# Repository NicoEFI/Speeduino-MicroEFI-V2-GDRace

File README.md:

# Speeduino-MicroEFI-V2-GDRace

Use Speeduino Firmware

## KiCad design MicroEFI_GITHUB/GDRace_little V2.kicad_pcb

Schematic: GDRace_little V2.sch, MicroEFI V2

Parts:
180k1, 180k2, 330k1, 330k2: R_Pack04; R_Array_Convex_4x0603
C1, C3: 1u; C_1206_HandSoldering
C2, C5: 22u; C_1206_HandSoldering
C4, C15, C18, C19, C20, C21, C22, C23, C30, C36: 0.1u; condo_C_1206_3216Metric_Pad1.42x1.75mm_HandSolder
C6: 100n; condo_C_1206_3216Metric_Pad1.42x1.75mm_HandSolder
C7: 100u; TantalC_SizeC_EIA-6032_HandSoldering
C11: 0.1uF; condo_C_1206_3216Metric_Pad1.42x1.75mm_HandSolder
C12: 4.7nF; condo_C_1206_3216Metric_Pad1.42x1.75mm_HandSolder
C13: 470p; condo_C_1206_3216Metric_Pad1.42x1.75mm_HandSolder
C14: 1u; condo_C_1206_3216Metric_Pad1.42x1.75mm_HandSolder
C16: 1n; condo_C_1206_3216Metric_Pad1.42x1.75mm_HandSolder
C17: 10n; condo_C_1206_3216Metric_Pad1.42x1.75mm_HandSolder
C24, C25, C26, C27, C28, C29, C31, C37: 0.22u; condo_C_1206_3216Metric_Pad1.42x1.75mm_HandSolder
D1: V68MLA1206H; Fuse_SMD1206_Reflow
D2, D7: Schottly-SS12; D_SMA_Handsoldering
D3: 3SMAJ5931B; do214ac
D4, D5, D6, D8, D11, D12, D13: 1N4001; D_MELF
D9: ZENER; do214ac
D10: 1N5819; SOD-123
D14: LED; LED_1206_3216Metric
F1: Polyfuse; Fuse_Bourns_MF-SM_9.5x6.71mm
GNDREF1, GNDREF2: CONN_01X01; MountingHole_3.2mm_M3_Pad_Via
J2: USB; JST_PH_B4B-PH-K_1x04_P2.00mm_Vertical
JP1, JP2: JUMPER; SolderJumper-2_P1.3mm_Open_RoundedPad1.0x1.5mm
JP3, JP4, JP5, JP7, JP8: JUMPER3; SolderJumper-3_P1.3mm_Open_RoundedPad1.0x1.5mm_NumberLabels
L1, L2, L3: 10uH; L_1206_3216Metric_Pad1.42x1.75mm_HandSolder
Q1, Q2, Q3: VND5N07
Q6, Q7: ISL9V5036S3S; TO-263-ingnition
R1: 470; resistance_R_1206_3216Metric_Pad1.42x1.75mm_HandSolder
R2, R4, R5, R9, R20, R41, R42: 200; resistance_R_1206_3216Metric_Pad1.42x1.75mm_HandSolder
R3, R11, R47: 2.2k; resistance_R_1206_3216Metric_Pad1.42x1.75mm_HandSolder
R6, R22: 10k; resistance_R_1206_3216Metric_Pad1.42x1.75mm_HandSolder
R10: 120; resistance_R_1206_3216Metric_Pad1.42x1.75mm_HandSolder
R13, R15, R23, R24, R32: 1k; resistance_R_1206_3216Metric_Pad1.42x1.75mm_HandSolder
R16, R17, R21, R43: 47k; resistance_R_1206_3216Metric_Pad1.42x1.75mm_HandSolder
R18, R19: 10k; R_2010_5025Metric
R25, R26: 100k; resistance_R_1206_3216Metric_Pad1.42x1.75mm_HandSolder
R27, R28, R45: 68k; resistance_R_1206_3216Metric_Pad1.42x1.75mm_HandSolder
R29, R30: 15R; resistance_R_1206_3216Metric_Pad1.42x1.75mm_HandSolder
R31: 3.9k; resistance_R_1206_3216Metric_Pad1.42x1.75mm_HandSolder
R33, R34: 2.49k; resistance_R_1206_3216Metric_Pad1.42x1.75mm_HandSolder
R35, R36, R37, R38, R39, R40, R44, R46: 470R; resistance_R_1206_3216Metric_Pad1.42x1.75mm_HandSolder
U1: LM2940T-5.0; sot223
U2: SN65HVD230; SOIC-8_3.9x4.9mm_P1.27mm
U3: MPX4250; MPXH6250A6U
U4: Molex48; connecteurMolex48
U5: Teensy3.5; Teensy35_36_sansSMD
U6, U7, U9, U13: IRLML0030TRPbF; IRLML0030_sot23
U8: MAX9926; QSOP-16_3.9x4.9mm_P0.635mm
U10: TC4424; SOIC-8_3.9x4.9mm_P1.27mm
U11, U12: LMV324; TSSOP-14_4.4x5mm_P0.65mm

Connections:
/3.3V: D10.1, R3.1, R11.1, R13.1, R15.1, R47.1, U5.15, U5.26, U11.4, U12.4
/5V: C7.1, C14.1, C15.1, C17.1, D9.1, F1.1, JP3.3, L2.1, R1.1, U5.53, U8.14 (vcc), U10.6 (VDD)
/5VSENSOR: C11.1, L2.2, R33.1, R34.1, U3.2, U4.2A1, U4.2A2, U4.2A3, U4.2A4
/12VPUISSANCE: C2.1, D2.1, D3.1, D7.1, JP3.1, U1.1
/12V_BATT_APRES_RELAIS: C1.1, D11.1 (K), L1.1, R31.1, U4.2L3, U4.2L4
/BARO: C19.1, JP2.2, R36.2
/BARO_3.3V: U5.42, U11.1, U11.2
/BARO_5V: 180k1.4, C25.1, R36.1
/BATTERY_REF_3.3V: U5.43, U11.8, U11.9
/BATTERY_REF_5V: 180k1.1, C26.1, R37.1
/BOOST: D11.2 (A), Q1.2 (D), U4.2C3
/BOOST_CPU: R5.1, R45.1, U5.48
/Btn_carto: D6.1 (K), U4.2K1
/Btn_carto_CPU: D6.2 (A), D8.1 (K), R11.2, U5.14
/Btn_depart: D4.1 (K), U4.2K2
/Btn_depart_CPU: D4.2 (A), D5.1 (K), R3.2, U5.16
/CAN_H: JP1.1, JP7.1, U2.7
/CAN_L: JP8.1, R10.2, U2.6
/CAN_RX_CPU: U2.4, U5.6
/CAN_TX_CPU: U2.1, U5.5
/CLT_3.3V: U5.47, U12.8, U12.9
/CLT_5V: 180k2.1, C28.1, R39.1
/CMD_RELAY_FUEL: U4.2G3, U6.3
/CMD_RELAY_FUEL_CPU: R41.1, U5.35
/D+: J2.3, U5.87
/D-: J2.2, U5.88
/DASH_CANH_TX_CPU: JP7.2, U4.2C1
/DASH_CANL_RX_CPU: JP8.2, U4.2C2
/FAN1: U4.2G1, U7.3
/FAN1_CPU: R9.1, U5.19
/FAN2: U4.2H1, U13.3
/FAN2_CPU: R42.1, U5.18
/GNDSENSOR: C11.2, C13.2, C18.2, C19.2, C20.2, C21.2, C22.2, C23.2, C24.2, C25.2, C26.2, C27.2, C28.2, C29.2, C30.2, C31.2, C36.2, C37.2, L3.2, R32.2, U3.3, U4.2B1, U4.2B2, U4.2B3, U4.2B4
/IAT_3.3V: U5.45, U12.13, U12.14
/IAT_5V: 180k2.2, C29.1, R40.1
/IGN_A_CPU: R23.1, U5.21
/IGN_B_CPU: R24.1, U5.20
/IGN_cyl_1_4: Q6.2, U4.2M4
/IGN_cyl_2_3: Q7.2, U4.2M3
/INJ_A_CPU: R2.1, R27.1, U5.22
/INJ_B_CPU: R4.1, R28.1, U5.30
/INJ_cyl_1_4: Q2.2 (D), U4.2M2
/INJ_cyl_2_3: Q3.2 (D), U4.2M1
/MAP: C30.1, R44.2, U4.2F3
/MAP_3.3V: U5.46, U12.6, U12.7
/MAP_5V: 180k2.3, C31.1, R44.1
/P_Oil_sw: D12.1 (K), U4.2K3
/P_Oil_sw_CPU: D12.2 (A), D13.1 (K), R47.2, U5.17
/RESET: C12.1, D10.2, R13.2, U5.29
/RX2_CPU: JP8.3, U5.12
/SMOT++: R18.1, U4.2D2
/SMOT--: R19.1, U4.2D1
/SMOT_CPU: R15.2, U5.8, U8.4 (out1)
/TACHO: R22.2, U4.2G2, U9.3
/TACHO_CPU: R20.1, U5.13
/TAIR: C23.1, R34.2, R40.2, U4.2E2
/TEAU: C22.1, R33.2, R39.2, U4.2E1
/TPS1: C21.1, R38.2, U4.2F1
/TPS1_3.3V: U5.41, U11.13, U11.14
/TPS1_5V: 180k1.2, C27.1, R38.1
/TX2_CPU: JP7.3, U5.11
/VARlaunch: C18.1, R35.2, U4.2F2
/VARlaunch_3.3V: U5.44, U11.6, U11.7
/VARlaunch_5V: 180k1.3, C24.1, R35.1
/VUSB: J2.1, U5.54
/WBO2: C36.1, R46.2, U4.2E3
/WBO2_3.3V: U5.49, U12.1, U12.2
/WBO2_5V: 180k2.4, C37.1, R46.1
GNDREF: 330k1.5, 330k1.6, 330k1.7, 330k1.8, 330k2.5, 330k2.6, 330k2.7, 330k2.8, C1.2, C2.2, C3.2, C4.2, C5.2, C6.2, C7.2, C12.2, C14.2, C15.2, C17.2, D1.2, D3.2, D5.2 (A), D8.2 (A), D9.2, D13.2 (A), D14.1, GNDREF1.1, GNDREF2.1, J2.4, L3.1, Q1.3 (S), Q2.3 (S), Q3.3 (S), Q6.3, Q7.3, R6.2, R16.2, R17.2, R21.2, R25.1, R26.2, R27.2, R28.2, R43.2, R45.2, U1.2, U1.4, U2.2, U4.2L1, U4.2L2, U5.1, U5.27, U5.39, U6.2, U7.2, U8.1 (int_thrs1), U8.3 (bias1), U8.6 (bias2), U8.8 (int_thrs2), U8.11 (gnd), U8.13 (zero_en), U9.2, U10.3 (GND), U11.11, U12.11, U13.2
unnamed: 180k1.5, 330k1.4, U11.3
unnamed: 180k1.6, 330k1.3, U11.5
unnamed: 180k1.7, 330k1.2, U11.12
unnamed: 180k1.8, 330k1.1, U11.10
unnamed: 180k2.5, 330k2.4, U12.3
unnamed: 180k2.6, 330k2.3, U12.5
unnamed: 180k2.7, 330k2.2, U12.12
unnamed: 180k2.8, 330k2.1, U12.10
unnamed: C3.1, C4.1, D1.1, D2.2, L1.2
unnamed: C5.1, C6.1, D7.2, F1.2, U1.3
unnamed: C13.1, JP2.1, U3.4
unnamed: C16.1, R19.2, U8.15 (in1-)
unnamed: C16.2, R18.2, U8.16 (in1+)
unnamed: C20.1, R31.2, R32.1, R37.2
unnamed: D14.2, R1.2
unnamed: JP1.2, R10.1
unnamed: JP3.2, R22.1
unnamed: JP4.1, U10.7 (OUTA)
unnamed: JP4.2, R29.1
unnamed: JP4.3, R23.2, R25.2, U10.2 (INA)
unnamed: JP5.1, U10.5 (OUTB)
unnamed: JP5.2, R30.1
unnamed: JP5.3, R24.2, R26.1, U10.4 (INB)
unnamed: Q1.1 (G), R5.2
unnamed: Q2.1 (G), R2.2
unnamed: Q3.1 (G), R4.2
unnamed: Q6.1, R29.2
unnamed: Q7.1, R30.2
unnamed: R6.1, U2.8
unnamed: R16.1, R41.2, U6.1
unnamed: R9.2, R17.1, U7.1
unnamed: R20.2, R21.1, U9.1
unnamed: R42.2, R43.1, U13.1

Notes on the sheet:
Bouton switch
Capteur pression
Capteur régime et cam
Alimentation
VND14NV04
12V_BATT_APRES_RELAIS_CONTACT
BATT
Fusible
Ventilo
ex : Pilotage ventilo 1
Interrupteur alim calculateur
FGP3440G2_F085 ISL9V5036S3S TO-263-2
1N5819HW-7-F
connecteur USB MUSB-D111-30 mouser + Connecteur micro-USB B mâle à souder (gotronic)
jack 3.5 LUMBERG = 1502 02 CUI Devices = SJ5-43502PM cable DELOCK 83182
ok fichier init
PFSM.050.2
ACZRA4734-HF 5.6V
100k?
manque liason entre 3.3v et vcc sur le pcb
pinWarnOil

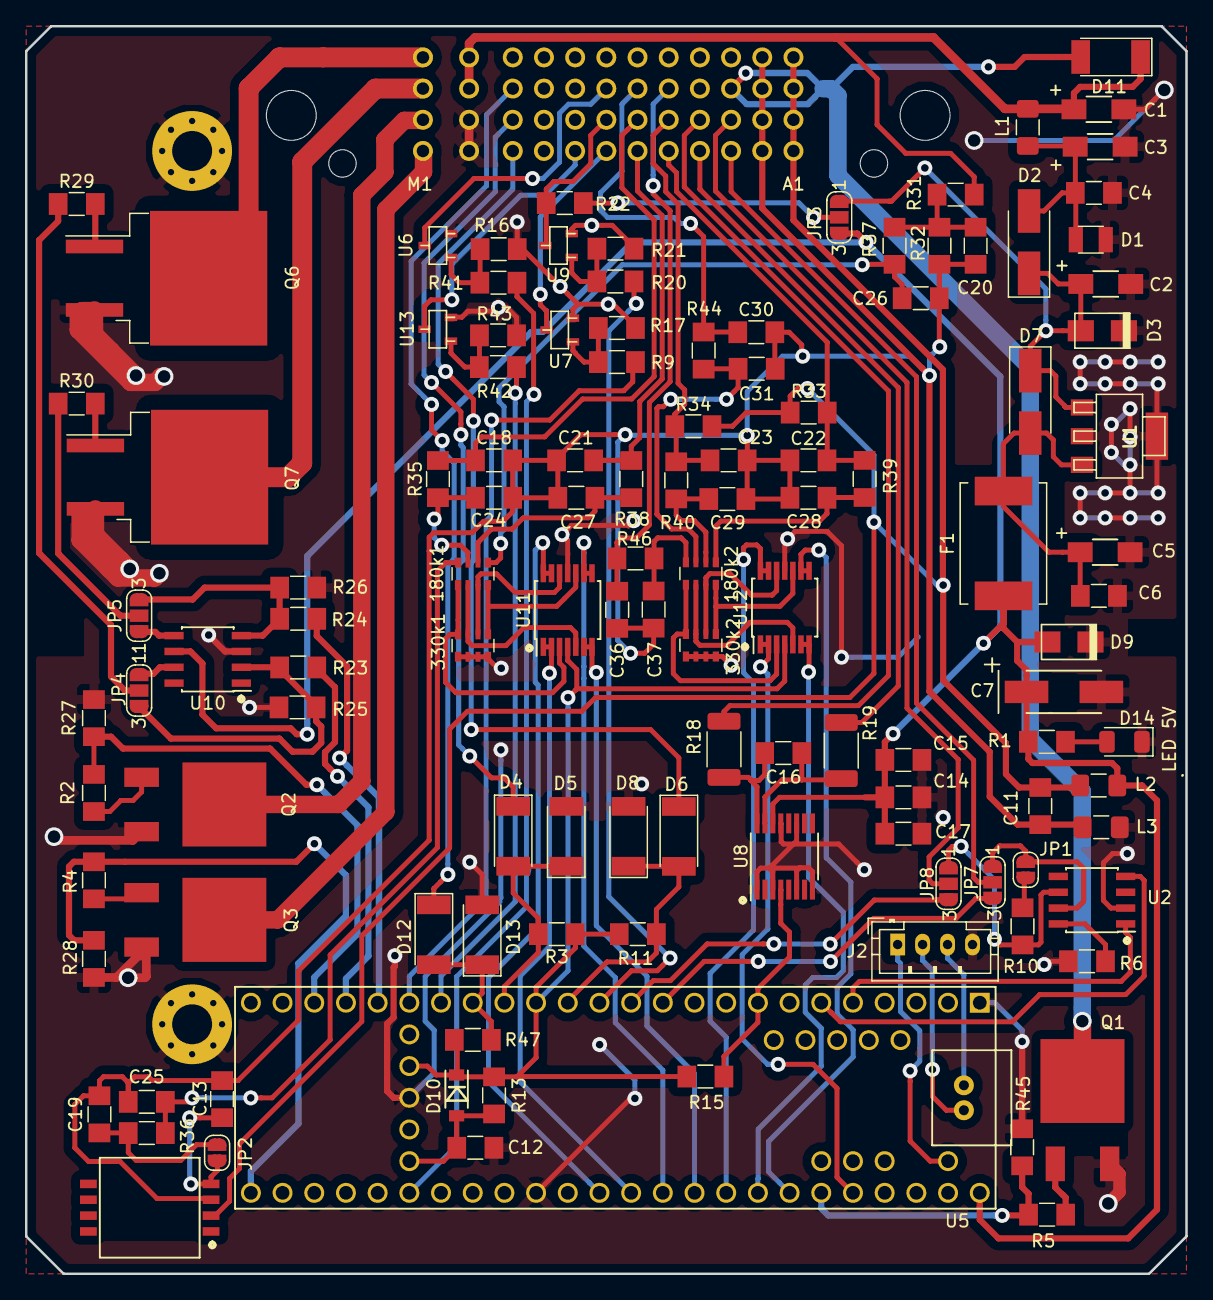
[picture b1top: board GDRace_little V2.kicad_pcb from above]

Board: 2 copper layers, 93.0 x 100.0 mm, 123 parts (0 on the bottom side), 102 nets.

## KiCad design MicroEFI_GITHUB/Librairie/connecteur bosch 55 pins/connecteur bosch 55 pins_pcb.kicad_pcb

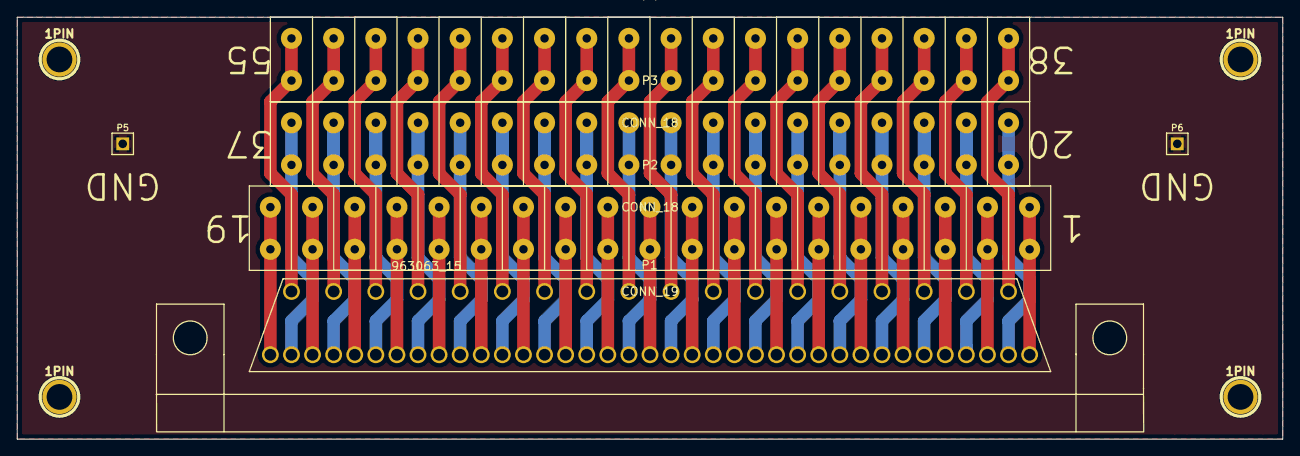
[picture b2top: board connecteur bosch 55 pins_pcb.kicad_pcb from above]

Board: 2 copper layers, 150.0 x 50.0 mm, 10 parts (0 on the bottom side), 56 nets.

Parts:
1PIN, 1PIN#2, 1PIN#3, 1PIN#4: P***; 1pin
P1: 963063_15; connecteur bosch 55 pins 963063-15
P2: CONN_19; CON19X5
P3, P4: CONN_18; CON18X5
P5, P6: CONN_1; PIN_ARRAY_1

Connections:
GND: P5.1, P6.1
unnamed: P1.11, P2.11
unnamed: P1.1, P2.1
unnamed: P1.2, P2.2
unnamed: P1.3, P2.3
unnamed: P1.4, P2.4
unnamed: P1.5, P2.5
unnamed: P1.6, P2.6
unnamed: P1.7, P2.7
unnamed: P1.8, P2.8
unnamed: P1.9, P2.9
unnamed: P1.10, P2.10
unnamed: P1.55, P4.18
unnamed: P1.12, P2.12
unnamed: P1.13, P2.13
unnamed: P1.14, P2.14
unnamed: P1.15, P2.15
unnamed: P1.16, P2.16
unnamed: P1.17, P2.17
unnamed: P1.18, P2.18
unnamed: P1.19, P2.19
unnamed: P1.20, P3.1
unnamed: P1.21, P3.2
unnamed: P1.44, P4.7
unnamed: P1.34, P3.15
unnamed: P1.35, P3.16
unnamed: P1.36, P3.17
unnamed: P1.37, P3.18
unnamed: P1.38, P4.1
unnamed: P1.39, P4.2
unnamed: P1.40, P4.3
unnamed: P1.41, P4.4
unnamed: P1.42, P4.5
unnamed: P1.43, P4.6
unnamed: P1.22, P3.3
unnamed: P1.45, P4.8
unnamed: P1.46, P4.9
unnamed: P1.47, P4.10
unnamed: P1.48, P4.11
unnamed: P1.49, P4.12
unnamed: P1.50, P4.13
unnamed: P1.51, P4.14
unnamed: P1.52, P4.15
unnamed: P1.53, P4.16
unnamed: P1.54, P4.17
unnamed: P1.33, P3.14
unnamed: P1.23, P3.4
unnamed: P1.24, P3.5
unnamed: P1.25, P3.6
unnamed: P1.26, P3.7
unnamed: P1.27, P3.8
unnamed: P1.28, P3.9
unnamed: P1.29, P3.10
unnamed: P1.30, P3.11
unnamed: P1.31, P3.12
unnamed: P1.32, P3.13

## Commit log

2020-04-02 File
